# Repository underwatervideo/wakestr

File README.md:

# wakestr
 Voltage Regulator + RTC + Backup battery + Sleep and Wake

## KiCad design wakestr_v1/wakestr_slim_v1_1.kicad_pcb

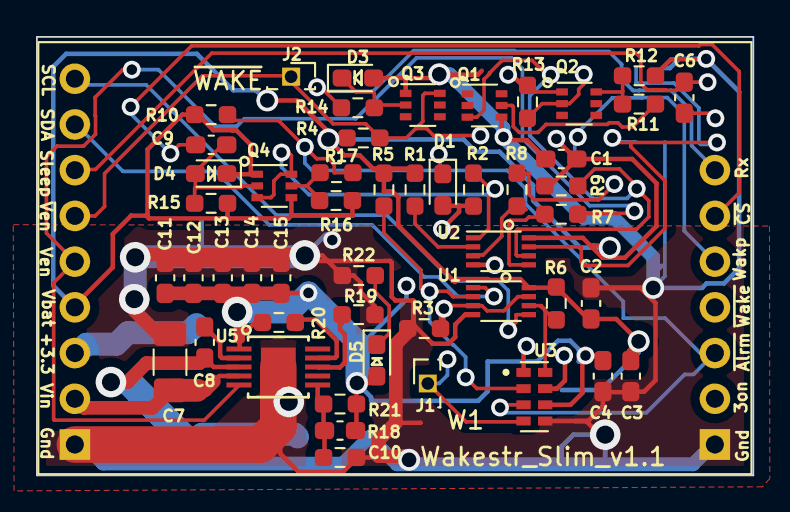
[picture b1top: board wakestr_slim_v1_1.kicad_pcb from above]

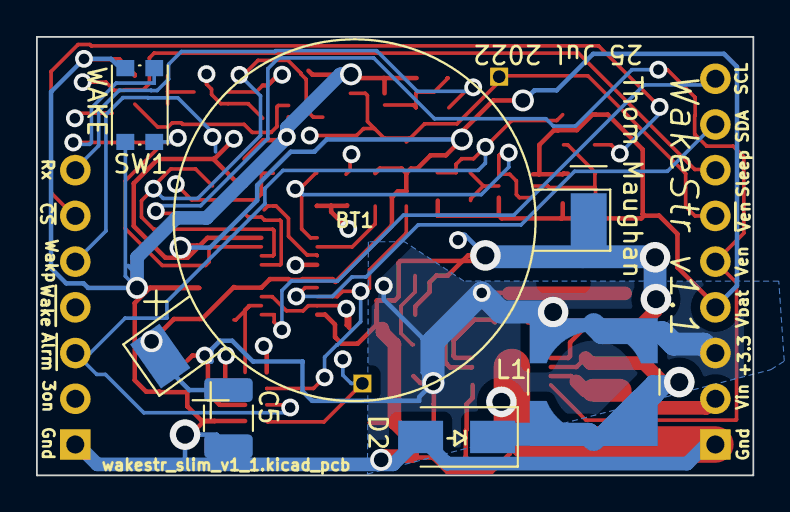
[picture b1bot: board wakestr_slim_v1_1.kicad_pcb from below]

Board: 4 copper layers, 39.8 x 24.4 mm, 56 parts (5 on the bottom side), 34 nets.

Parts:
BT1: ML2020_F1AN
C1, C2, C3, C4: 100nF; C_0603_1608Metric_Pad1.08x0.95mm_HandSolder
C5: 11mF CPH3225A; C_1210_3225Metric_Pad1.33x2.70mm_HandSolder
C6, C9, C11, C12, C13, C14, C15: 10uF; C_0603_1608Metric_Pad1.08x0.95mm_HandSolder
C7: 10uF 50v; C_1206_3216Metric_Pad1.33x1.80mm_HandSolder
C8: 0.47uF; C_0603_1608Metric_Pad1.08x0.95mm_HandSolder
C10: 10pF; C_0603_1608Metric_Pad1.08x0.95mm_HandSolder
D1, D3, D4: ‎B0240R‎; D_0603_1608Metric_Pad1.05x0.95mm_HandSolder
D2: B120-E3; D_SMA
D5: GREEN; LED_0603_1608Metric_Pad1.05x0.95mm_HandSolder
J1: EVNT; PinSocket_1x01_P1.27mm_Vertical
J2: ~{WAKE}; PinSocket_1x01_P1.27mm_Vertical
L1: MSS7341-123MLD; IND_MSS7341-563MLD
Q1, Q3: BC846BS; SOT-363_SC-70-6
Q2, Q4: BC856BS; SOT-363_SC-70-6
R1, R2, R4, R5, R6, R9, R12, R13, R14, R15, R16, R20: 100K; R_0603_1608Metric_Pad0.98x0.95mm_HandSolder
R3, R21: 1M; R_0603_1608Metric_Pad0.98x0.95mm_HandSolder
R7, R8, R11, R17, R22: 10K; R_0603_1608Metric_Pad0.98x0.95mm_HandSolder
R10: 100K NS; R_0603_1608Metric_Pad0.98x0.95mm_HandSolder
R18: 562K; R_0603_1608Metric_Pad0.98x0.95mm_HandSolder
R19: 118K; R_0603_1608Metric_Pad0.98x0.95mm_HandSolder
SW1: WAKE; SW_Push_1P1T_NO_CK_KMR2
U1: NL7WB66USG; VSSOP-8_2.3x2mm_P0.5mm
U2: 74AUP1G74; VSSOP-8_2.3x2mm_P0.5mm
U3: RTC-RV-3032; IC_RV-3028-C7
U5: LT3991EMS-ADJ; MSOP-10_MSE
W1: Wakestr_Slim_v1.1; wakestr_slim_v1

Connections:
+3V3: C4.1, C10.1, C11.1, C12.1, C13.1, C14.1, C15.1, D5.2 (A), L1.1, R20.1, R21.1, U3.6 (VDD), U5.1 (BD), W1.3 (+3V3)
/+3Vx_ON: R3.2, U1.3, U1.7, W1.15 (+3V3_ON)
/BRD_WAKE_P: Q4.3 (C2), Q4.6 (C1), R2.2, U2.1 (C), W1.12 (WAKE_P)
/EVENT_CNT: J1.1, U3.4 (EVI)
/I2C_SCL: U1.5, W1.9 (I2C_SCL)
/I2C_SDA: U1.1, W1.8 (I2C_SDA)
/PWR GOOD: R20.2, U5.9 (PG)
/RX1_232: R14.1, W1.10 (SER_RX)
/VD2_I2C_SCL: R6.1, U1.6, U3.8 (SCL)
/VD2_I2C_SDA: R5.1, U1.2, U3.2 (SDA)
/VIN: C7.1, U5.4 (VIN), W1.2 (VIN)
/VREG_EN: R7.1, U5.5 (EN), W1.5 (VREG_EN)
/~BRD_WAKE: J2.1, Q3.6 (C1), R4.1, SW1.1, U2.7 (~PRE), W1.6 (~WAKE)
/~PROC_SLEEP: C6.1, W1.7 (PROC_SLEEP)
/~RTC_ALARM: R10.1, R17.1, U3.3 (~INT), W1.14 (~ALARM)
/~SLEEP: Q1.3 (C2), R9.1, U2.6 (~CLR)
/~SPI_CS: C9.1, W1.11 (~SPI_CS)
/~VREG_EN: R8.1, W1.13 (~VREG_EN)
GND: BT1.2 (-), C1.2, C2.2, C3.2, C4.2, C5.2, C7.2, C11.2, C12.2, C13.2, C14.2, C15.2, D1.2 (A), D2.2 (A), D3.2 (A), Q1.4 (E2), Q3.1 (E1), R2.1, R3.1, R12.2, R18.2, R19.1, R22.1, SW1.2, U1.4 (GND), U2.4 (GND), U3.5 (GND), U5.11 (GND), W1.1 (GND), W1.16 (GND)
unnamed: C6.2, D1.1 (K), Q2.2 (B1), R13.2
unnamed: C8.1, U5.2 (BOOST)
unnamed: C8.2, D2.1 (K), L1.2, U5.3 (SW)
unnamed: C9.2, D4.2 (A), Q4.2 (B1), R15.2
unnamed: C10.2, R18.1, R21.2, U5.6 (FB)
unnamed: D3.1 (K), Q3.2 (B1), R14.2
unnamed: D5.1 (K), R22.2
unnamed: Q1.5 (B2), R11.1
unnamed: Q2.6 (C1), R11.2, R12.1
unnamed: Q4.5 (B2), R16.2, R17.2
unnamed: R1.1, U2.2 (D)
unnamed: R7.2, U2.5 (Q)
unnamed: R8.2, U2.3 (~Q)
unnamed: R19.2, U5.8 (RT)
VCC: BT1.1 (+), C1.1, C2.1, C3.1, C5.1, D4.1 (K), Q2.1 (E1), Q4.1 (E1), Q4.4 (E2), R1.2, R4.2, R5.2, R6.2, R9.2, R10.2, R13.1, R15.1, R16.1, U1.8 (VCC), U2.8 (VCC), U3.1 (Vbackup), W1.4 (+3V_COIN)

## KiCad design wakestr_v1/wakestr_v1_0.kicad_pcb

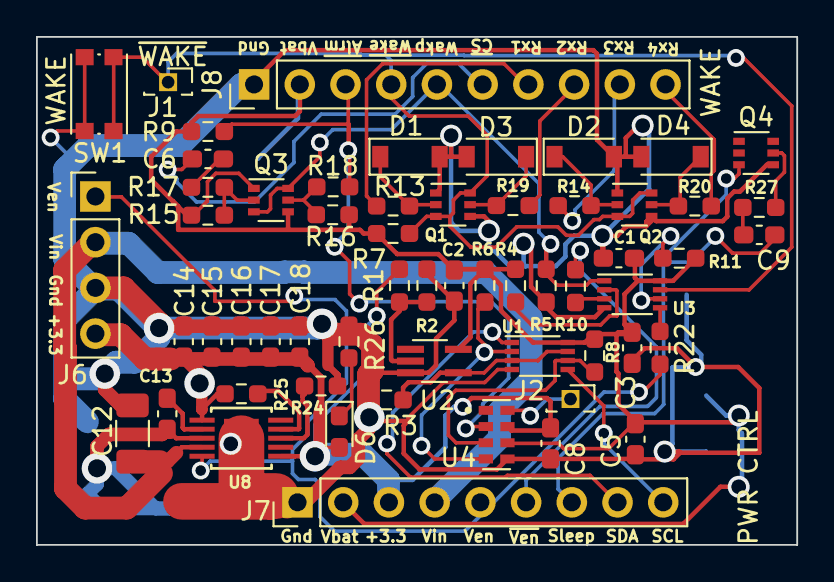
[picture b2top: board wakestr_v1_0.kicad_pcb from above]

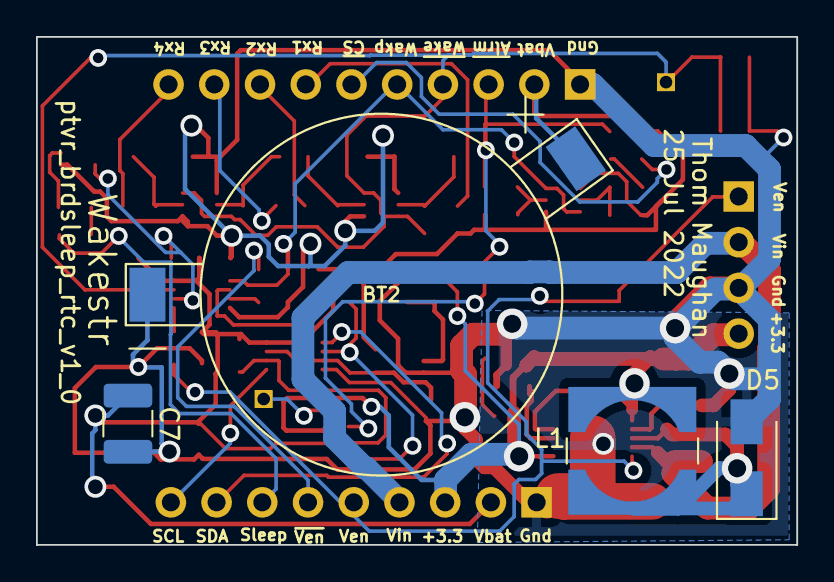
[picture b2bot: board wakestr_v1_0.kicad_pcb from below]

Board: 2 copper layers, 42.2 x 28.2 mm, 62 parts (4 on the bottom side), 40 nets.

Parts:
BT2: ML2020_F1AN
C1, C2, C3, C5, C6, C8, C9: 100nF; C_0603_1608Metric_Pad1.08x0.95mm_HandSolder
C7: 11mF CPH3225A; C_1210_3225Metric_Pad1.33x2.70mm_HandSolder
C12: 10uF 50v; C_1206_3216Metric_Pad1.33x1.80mm_HandSolder
C13: 0.47uF; C_0603_1608Metric_Pad1.08x0.95mm_HandSolder
C14, C15, C16, C17, C18: 10uF; C_0603_1608Metric_Pad1.08x0.95mm_HandSolder
D1, D2, D3, D4: BAT43W-V; D_SOD-123
D5: B120-E3; D_SMA
D6: GREEN; LED_0603_1608Metric_Pad1.05x0.95mm_HandSolder
J1: ~{WAKE}; PinSocket_1x01_P1.27mm_Vertical
J2: EVNT; PinSocket_1x01_P1.27mm_Vertical
J6: iVREG; PinHeader_1x04_P2.54mm_Vertical
J7: PWR CTRL; PinHeader_1x09_P2.54mm_Vertical
J8: WAKE; PinHeader_1x10_P2.54mm_Vertical
L1: MSS7341-123MLD; IND_MSS7341-563MLD
Q1, Q2, Q4: BC846BS; SOT-363_SC-70-6
Q3: BC856BS; SOT-363_SC-70-6
R1, R4, R5, R6, R7, R8, R11, R13, R14, R15, R16, R19, R20, R25: 100K; R_0603_1608Metric_Pad0.98x0.95mm_HandSolder
R2, R3: 1M; R_0603_1608Metric_Pad0.98x0.95mm_HandSolder
R9: 100K NS; R_0603_1608Metric_Pad0.98x0.95mm_HandSolder
R10, R17, R18, R22, R26, R27: 10K; R_0603_1608Metric_Pad0.98x0.95mm_HandSolder
R24: 118K; R_0603_1608Metric_Pad0.98x0.95mm_HandSolder
SW1: WAKE; SW_Push_1P1T_NO_CK_KMR2
U1: NL7WB66USG; VSSOP-8_2.3x2mm_P0.5mm
U2: 74AUP1G17; SOT-353_SC-70-5_Handsoldering
U3: 74AUP1G74; VSSOP-8_2.3x2mm_P0.5mm
U4: RTC-RV-3028-C7; IC_RV-3028-C7
U8: LT3991EMS-3.3; MSOP-10_MSE

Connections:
+3V3: C8.1, C14.1, C15.1, C16.1, C17.1, C18.1, D6.2 (A), J6.4, J7.3, L1.1, R1.2, R25.1, U4.7 (VDD), U8.1 (BD), U8.6 (VOUT)
/+3V3_ON: R3.2, U1.3, U1.7, U2.4
/BRD_WAKE_P: J8.5, Q3.3 (C2), Q3.6 (C1), R5.2, U3.1 (C)
/EVENT_CNT: J2.1, U4.8 (EVI)
/I2C_SCL: J7.9, U1.5
/I2C_SDA: J7.8, U1.1
/PROC_SLEEP: C9.1, J7.7
/PWR GOOD: R25.2, U8.9 (PG)
/RX1_232: J8.7, R13.1
/RX2_232: J8.8, R19.1
/RX3_232: J8.9, R14.1
/RX4_232: J8.10, R20.1
/VD2_I2C_SCL: R8.1, U1.6, U4.3 (SCL)
/VD2_I2C_SDA: R6.1, U1.2, U4.4 (SDA)
/VIN: C12.1, J6.2, J7.4, U8.4 (VIN)
/VREG_EN: J6.1, J7.5, R22.1, U8.5 (EN)
/~BRD_WAKE: J1.1, J8.4, Q1.3 (C2), Q1.6 (C1), Q2.3 (C2), Q2.6 (C1), R7.1, SW1.1, U3.7 (~PRE)
/~RTC_ALARM: J8.3, R9.1, R18.1, U4.2 (INT~)
/~SLEEP: Q4.3 (C2), R11.1, U3.6 (~CLR)
/~SPI_CS: C6.1, J8.6
/~VREG_EN: J7.6, R10.1
GND: BT2.2 (-), C1.2, C2.2, C3.2, C5.2, C7.2, C8.2, C12.2, C14.2, C15.2, C16.2, C17.2, C18.2, D1.2 (A), D2.2 (A), D3.2 (A), D4.2 (A), D5.2 (A), J6.3, J7.1, J8.1, Q1.1 (E1), Q1.4 (E2), Q2.1 (E1), Q2.4 (E2), Q4.4 (E2), R2.1, R3.1, R5.1, R24.1, R26.1, SW1.2, U1.4 (GND), U2.3 (GND), U3.4 (GND), U4.5 (GND), U8.11 (GND)
unnamed: C6.2, R17.1
unnamed: C9.2, R27.1
unnamed: C13.1, U8.2 (BOOST)
unnamed: C13.2, D5.1 (K), L1.2, U8.3 (SW)
unnamed: D1.1 (K), Q1.2 (B1), R13.2
unnamed: D2.1 (K), Q2.2 (B1), R14.2
unnamed: D3.1 (K), Q1.5 (B2), R19.2
unnamed: D4.1 (K), Q2.5 (B2), R20.2
unnamed: D6.1 (K), R26.2
unnamed: Q3.2 (B1), R15.2, R17.2
unnamed: Q3.5 (B2), R16.2, R18.2
unnamed: Q4.5 (B2), R27.2
unnamed: R1.1, R2.2, U2.2
unnamed: R4.1, U3.2 (D)
unnamed: R10.2, U3.3 (~Q)
unnamed: R22.2, U3.5 (Q)
unnamed: R24.2, U8.8 (RT)
VCC: BT2.1 (+), C1.1, C2.1, C3.1, C5.1, C7.1, J7.2, J8.2, Q3.1 (E1), Q3.4 (E2), R4.2, R6.2, R7.2, R8.2, R9.2, R11.2, R15.1, R16.1, U1.8 (VCC), U2.5 (VCC), U3.8 (VCC), U4.6 (Vbackup)

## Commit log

2022-07-31 Checkin from wakester to wakestr repo
    Checkin from wakester to wakestr repo
